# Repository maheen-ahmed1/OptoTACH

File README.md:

# OptoTACH
### A Precision Non-Contact Optical Tachometer Built Entirely Without a Microcontroller

**OptoTACH** is a discrete hardware engineering project that implements a full-featured, 4-digit optical tachometer (0–9999 RPM / RPS / Event Counter) using **pure CMOS logic and analog timing circuits**—completely free of microcontrollers, firmware, and software dependencies.

## ⚡ Showcase & Physical Verification

| 3D CAD Visualization | Assembled Hardware Prototype | Live Calibration vs Commercial Bench Standard |
| :---: | :---: | :---: |
|  |  |  |
| *Raytraced 3D model in KiCad* | *Physical board with socketed DIP ICs* | *Benchmark vs Lutron DT-2236 (2267 vs 2280 RPM)* |

### 🎬 Live Bench Demo
The board measures the rotational velocity of a high-speed cooling fan equipped with a reflective marker. The reading automatically updates every 4 seconds with zero display jitter.

<p align="center">
  
  <br>
  <em>Live demonstration: OptoTACH benchmarked alongside an industrial Lutron DT-2236 photo/contact tachometer.</em>
  <br>
  <a href="media/optotach_demo.mp4">▶️ Download / View Full 1080p Demo Video (2 min 50 sec, 35 MB MP4)</a>
</p>

## 🔄 Inspiration & Circuit Redesign (Overcoming IC Obsolescence)

This project was inspired by the original design published by [Mousa Simple Projects (August 2020)](https://www.mousa-simple-project.com/2020/08/non-contact-tachometer-without.html). However, **the schematic in OptoTACH is fundamentally redesigned** due to component obsolescence and supply-chain constraints.

### The Problem: Obsolescence of the CD40110
The original 2020 design relied on 4 × **CD40110** integrated circuits. The CD40110 incorporates an up/down decade counter, 7-segment decoder, and an internal display latch into a single package. Because the CD40110 has been largely discontinued and is unobtainable in South Asian markets (including Bangladesh), building the circuit directly from the original schematic was impossible.

### The Solution: Re-engineering with the CD4026BE
OptoTACH replaces the obsolete chips with the widely available **CD4026BE** (decade counter with 7-segment decoder). However, **the CD4026 has no internal display latch**. Without a latch, displaying raw pulses as they accumulate during a 1-second counting window would result in an illegible rolling blur.

To solve this without adding extra counter or latch ICs, OptoTACH introduces a synchronized **digital gating & display blanking mechanism**:

| Feature / Subsystem | Original Mousa Circuit (2020) | OptoTACH v1.0 (Redesigned) | Why the Change Matters |
| :--- | :--- | :--- | :--- |
| **Counter ICs** | 4 × **CD40110** (Obsolete / Discontinued) | 4 × **CD4026BE** (Standard / Readily Available) | Overcomes supply-chain unavailability |
| **Display Storage** | Internal CD40110 Display Latch | **Digital Blanking Window (CD4026 Pin 3 `DE`)** | Enables rock-solid readout without latch ICs |
| **Gating Timing** | Continuous asynchronous display | **1.000 s Gate once every 4.000 s** | Digits blank during 1 s count; hold static for 3 s |
| **Gate Derivation** | R/C & basic logic | **Exact Quartz Binary Division** ($Q_4 \text{ AND } Q_5$) | Zero drift (<0.005%) derived from 32.768 kHz crystal |
| **Silicon Overhead** | Spare gates left unused | **100% Gate Utilization of CD4093** | Blanking & gating use spare Schmitt NAND gates (0 added ICs) |
| **Operating Modes** | Single fixed mode | **3 Switchable Modes** (RPM, RPS, Counter) | Onboard 4-position DIP switch (`SW1`) |
| **Physical PCB** | Prototype breadboard / perfboard | **Production 2-Layer 100×100mm PCB** | Socketed ICs, ground planes, DFM compliant |

## 🎯 Key Specifications

| Parameter | Specification | Notes / Hardware Source |
| :--- | :--- | :--- |
| **Measurement Range** | **0 – 9,999 RPM** (or RPS / Events) | 4-digit common-cathode 7-segment display (`DS1`–`DS4`) |
| **Measurement Modes** | **RPM**, **RPS**, and **Continuous Counter** | Configured via onboard 4-way DIP switch (`SW1`) |
| **Sensor Type** | Vishay **TCRT5000** Optical Reflex Sensor | 950 nm IR emitter + phototransistor; 0.2–15 mm sensing gap |
| **Timebase Reference** | **32.768 kHz Quartz Crystal** (`Y1`) | Division via dual `CD4060BE` ripple counters; drift < 0.005% |
| **Measurement Window** | **1.000 s Gate every 4.000 s** | Digital AND gating (`Q4` & `Q5`) via Schmitt NAND (`CD4093`) |
| **Multiplier Ratio** | **×60 Pulse Multiplier** (for direct RPM readout) | Dual `CD4017` cascade gating a high-frequency `NE555` burst |
| **Operating Supply** | **5.0 V – 6.0 V DC** (4 × AA cells or bench PSU) | Reverse-polarity protected with onboard bulk decoupling |
| **PCB Dimensions** | **100.0 × 100.0 mm**, 2 layers, FR-4 | 100% Through-Hole Technology (THT) for easy hand assembly |
| **Fabrication State** | **JLCPCB Ready** (DRC 0/0, ERC 0/0) | Gerbers, BOM, drill files, and assembly maps verified |

## 🧠 System Architecture & Circuit Operation

```
                                    +-----------------------------------------------+
                                    |               MODE SELECT (SW1)               |
                                    |   RPM: 0110   |   RPS: 0101   |   CNT: 1000   |
                                    +-----------------------+-----------------------+
                                                            |
 [Target Shaft]                                             v
  +----------+       +---------------+       +------------------------------+       +-------------------+
  |Reflective| ----> |   TCRT5000    | ----> | Optical Conditioning & Burst | ----> |   4-Digit CD4026  |
  |  Marker  |       | Sensor (U1)   |       | Multiplier (NE555 + CD4017)  |       |   Counter Chain   |
  +----------+       +---------------+       +------------------------------+       | (U11,U12,U13,U14) |
                                                            ^                       +---------+---------+
                                                            |                                 |
 [Quartz Timebase]                                          | Gate Signal                     v
  +----------+       +---------------+       +--------------+---------------+       +-------------------+
  |32.768 kHz| ----> | 2 x CD4060BE  | ----> |   CD4093 NAND Logic Gate     | ----> | 4 x 7-Segment LED |
  | Crystal  |       | Dividers      |       |  (1.0s Gate / 4.0s Period)   |       |  Displays (DS1-4) |
  +----------+       +---------------+       +------------------------------+       +-------------------+
                                                            | Display Blanking
                                                            +---------------------------------> Pin 3 (DE)
```

### 1. Digital Quartz Timebase
The 1.000-second count window is derived with zero passive R/C timing dependencies:
$$\text{Gate Period} = \frac{32,768\text{ Hz}}{2^{12} \times 2^{5}} = 0.25\text{ Hz} \quad (4.000\text{ seconds})$$
A logical AND combination of the `CD4060` outputs $Q_4$ (0.5 Hz, 50% duty) and $Q_5$ (0.25 Hz, 50% duty) generates an active gate window of exactly $1.000\text{ s}$ once every $4\text{ s}$.

### 2. ×60 Pulse Burst Multiplier (RPM Conversion)
At 1 pulse per revolution, counting for 1 second yields Revolutions Per Second (RPS). To display Revolutions Per Minute (RPM) directly without software:
1. Each detected optical edge triggers a high-speed `NE555` oscillator burst.
2. Two cascaded `CD4017` decade counters count exactly **60 pulses** and shut off the oscillator.
3. The resulting 60 pulses feed into the `CD4026` display counter chain for every revolution, achieving an exact direct RPM conversion.

### 3. Mode Selection Truth Table
An onboard 4-pole DIP switch (`SW1`) configures the instrument mode:

| Mode | Switch 1 | Switch 2 | Switch 3 | Switch 4 | Functional Behavior |
| :--- | :---: | :---: | :---: | :---: | :--- |
| **RPM** | OFF | **ON** | **ON** | OFF | 1 s gate, ×60 burst multiplier enabled (Direct RPM readout) |
| **RPS** | OFF | **ON** | OFF | **ON** | 1 s gate, direct sensor pulse routing (Direct RPS readout) |
| **CNT** | **ON** | OFF | OFF | OFF | Continuous event counter; display permanently enabled |

### 4. Integrated Circuit Roles & Signal Flow

| RefDes | Part Number | Package | Primary Circuit Role / Subsystem |
| :--- | :--- | :--- | :--- |
| **`U1`** | **TCRT5000** | 4-pin Optical | Reflective optical sensor (950 nm IR LED + phototransistor) |
| **`U2`** | **CD4093BE** | DIP-14 | Quad 2-input Schmitt NAND (gating window logic & display blanking) |
| **`U3`** | **PC817** | DIP-4 | Optical trigger galvanic isolation & pulse conditioning |
| **`U4`** | **NE555P** | DIP-8 | Burst gate monostable latch (active burst control) |
| **`U5`** | **PC817** | DIP-4 | Gate reset isolation & pulse transmission |
| **`U6`** | **NE555P** | DIP-8 | Astable burst clock oscillator ($f \approx 4.8\text{ kHz}$) |
| **`U7`** | **CD4017BE** | DIP-16 | 5-stage Johnson decade counter (burst units: $\div 10$) |
| **`U8`** | **CD4017BE** | DIP-16 | 5-stage Johnson decade counter (burst tens: $\div 6$, auto-reset at 60) |
| **`U9`** | **CD4060BE** | DIP-16 | 14-stage ripple counter & 32.768 kHz oscillator ($\div 2^{12} = 8\text{ Hz}$) |
| **`U10`** | **CD4060BE** | DIP-16 | 14-stage ripple counter ($\div 2^4 = 0.5\text{ Hz}, \div 2^5 = 0.25\text{ Hz}$) |
| **`U11`** | **CD4026BE** | DIP-16 | Decade counter & 7-segment decoder (Digit 1 - LSD) |
| **`U12`** | **CD4026BE** | DIP-16 | Decade counter & 7-segment decoder (Digit 2 - Tens) |
| **`U13`** | **CD4026BE** | DIP-16 | Decade counter & 7-segment decoder (Digit 3 - Hundreds) |
| **`U14`** | **CD4026BE** | DIP-16 | Decade counter & 7-segment decoder (Digit 4 - MSD) |
| **`DS1–4`**| **7SEG-CC** | 10-pin DIP | 0.56" Common-Cathode red LED displays |

## 🔬 Bench Validation & Accuracy Analysis

The assembled hardware was benchmarked in an instrumentation laboratory using a calibrated **Lutron DT-2236 Photo/Contact Tachometer** on a variable-speed brushless DC blower:

| Reference Instrument (Lutron DT-2236) | OptoTACH v1.0 Measured Value | Absolute Deviation | Error (%) | Validation Result |
| :---: | :---: | :---: | :---: | :---: |
| **1,007 RPM** | **1,020 RPM** | +13 RPM | +1.29% | Within $\pm 1$ count ($\pm 60$ RPM) |
| **2,267 RPM** | **2,280 RPM** | +13 RPM | +0.57% | Within $\pm 1$ count ($\pm 60$ RPM) |
| **2,434 RPM** | **2,438 RPM** | +4 RPM | **+0.16%** | High-precision alignment |

> **Quantisation Theory:** In RPM mode with a 1-pulse target marker and a 1-second gate, the fundamental digital resolution is **60 RPM per count**. Any reading within $\pm 60$ RPM of the continuous reference is within theoretical limits. Increasing target markers (e.g., 2 or 4 reflective strips) scales resolution down proportionally.

## 📐 Schematic & Circuit Diagram

The complete schematic was designed in KiCad (clean ERC: 0 errors, 0 warnings).

<p align="center">
  
  <br>
  <em>OptoTACH v1.0 Full Schematic Sheet. Vector PDF available in <a href="fabrication/tach_v1.0_schematic.pdf">fabrication/tach_v1.0_schematic.pdf</a>.</em>
</p>

## 🛠️ PCB Layout & Hardware Design

The printed circuit board was designed from scratch in KiCad with rigorous DFM standards:

- **Dimensions:** 100 mm × 100 mm (optimised for JLCPCB 5-for-\$2 standard manufacturing tier)
- **Layer Stack:** 2 layers, 1.6 mm FR-4, 1 oz copper
- **Ground Strategy:** Solid continuous ground pours on both top and bottom layers, interconnected via stitched return vias
- **Corner Fillets:** Smooth $R = 5\text{ mm}$ rounded corners on `Edge.Cuts` for enclosure fit and ergonomic handling
- **Mounting:** 4 × M3 (3.2 mm NPTH) mounting holes routed with clear copper/keepout zones
- **Serviceability:** All 13 integrated circuits are socketed in dual-in-line (DIP) packages, allowing easy replacement or debugging
- **Silkscreen Guide:** Onboard mode selection table and resistor group markings embedded directly on `F.SilkS`

| Isometric Perspective | Top Layer Orthogonal | Bottom Layer / Solder Side |
| :---: | :---: | :---: |
|  |  |  |

> **Interactive 3D Viewer:** You can inspect and rotate the complete 3D assembly in your browser via GitHub's native 3D viewer by clicking [`media/optotach_3d_model.glb`](media/optotach_3d_model.glb).

## 📂 Repository Structure

```text
OptoTACH/
├── README.md                          # Repository portfolio overview & documentation
├── LICENSE                            # MIT Open Source Hardware License
├── .gitignore                         # KiCad EDA & OS build artifact filter
│
├── hardware/                          # KiCad Source Project (EDA Files)
│   ├── tach_v1.0.kicad_pro            # KiCad project definition
│   ├── tach_v1.0.kicad_sch            # Full schematic sheet (ERC: 0 errors)
│   ├── tach_v1.0.kicad_pcb            # PCB layout (DRC: 0 errors / 0 unconnected)
│   ├── tach_v1.0.kicad_dru            # DRC custom design rules
│   ├── tach_v1.0.kicad_prl            # Project local settings
│   ├── sym-lib-table & fp-lib-table   # Local symbol & footprint library tables
│   ├── tach_lib.kicad_sym             # Custom schematic symbol library
│   └── tach_fp.pretty/                # Custom footprint library (displays, ICs)
│
├── fabrication/                       # Ready-to-Order Manufacturing Package
│   ├── tach_v1.0_gerbers_jlcpcb.zip   # 1-Click Gerber & Drill archive for JLCPCB / PCBWay
│   ├── gerbers/                       # Unpacked RS-274X Gerber & Excellon drill files
│   ├── BOM_OptoTACH_v1.0.csv          # Complete structured Bill of Materials
│   ├── tach_v1.0_assembly.pdf         # Assembly and component reference drawing
│   ├── tach_v1.0_fitted_parts.pdf     # Visual parts fitting and orientation map
│   ├── tach_v1.0_fitted_parts.png     # High-resolution visual parts placement guide
│   ├── tach_v1.0_schematic.pdf        # High-resolution printable schematic sheet
│   └── SHOPPING_LIST.md               # Sourcing notes, LCSC part numbers & socket guide
│
├── simulation/                        # Behavioral Model & Timing Sweep Suite
│   ├── sweep.py                       # Behavioral Python simulation of counting dynamics
│   ├── mksvg.py                       # Vector SVG accuracy curve generator
│   ├── mkchart.py                     # Interactive HTML report generator
│   ├── sweep_report.html              # Standalone interactive browser accuracy report
│   ├── sweep.json                     # Raw sweep data points (0.5 Hz resolution)
│   ├── tach.net                       # Extracted netlist for timing trace
│   └── figures/                       # Rendered frequency & error curves
│
├── docs/                              # Technical Documentation
│   ├── OptoTACH_v1.0_Technical_Report.pdf # 38-page complete technical & verification report
│   ├── BRING_UP_GUIDE.md              # Staged bench test & troubleshooting procedure
│   └── TACHOMETER_ACCURACY_REPORT.md  # Timing simulation & quantisation study
│
└── media/                             # Visual & Interactive Demonstration Assets
    ├── optotach_demo.gif              # High-framerate looping README demonstration
    ├── optotach_demo.mp4              # Full 1080p bench demo video (35 MB H.264)
    ├── optotach_schematic.png         # High-resolution wiring schematic image
    ├── optotach_live_validation.jpg   # Benchmark capture vs Lutron DT-2236
    ├── optotach_prototype.jpeg        # Assembled hardware photograph
    ├── optotach_display_powered.jpeg  # Active 7-segment display photograph
    ├── optotach_3d_render.png         # KiCad 3D raytraced top view
    ├── optotach_3d_angle.png          # KiCad 3D angled view
    ├── optotach_3d_top.png            # KiCad 3D top view
    ├── optotach_3d_back.png           # KiCad 3D rear view
    ├── optotach_3d_model.glb          # Interactive 3D GLTF mesh model
    └── README_VIDEO_NOTE.md           # Video encoding & GitHub hosting notes
```

## 🚀 How to Recreate This Project

### 1. Order the PCB
1. Download [`fabrication/tach_v1.0_gerbers_jlcpcb.zip`](fabrication/tach_v1.0_gerbers_jlcpcb.zip).
2. Upload the ZIP file directly to [JLCPCB](https://jlcpcb.com/) or [PCBWay](https://www.pcbway.com/).
3. Default settings work out-of-the-box:
   - **Dimensions:** 100 × 100 mm
   - **Layers:** 2
   - **PCB Thickness:** 1.6 mm
   - **Solder Mask:** Black (or your choice of color)
   - **Silkscreen:** White

### 2. Source the Components
Review the detailed [Component Shopping List](fabrication/SHOPPING_LIST.md) and [BOM CSV](fabrication/BOM_OptoTACH_v1.0.csv). Key ICs and precision timing parts:

| Component | Quantity | Designation | Key Sourcing Notes |
| :--- | :---: | :--- | :--- |
| **CD4026BE** | 4 | `U11`, `U12`, `U13`, `U14` | Decade Counter / 7-Segment Decoder (DIP-16) |
| **CD4060BE** | 2 | `U9`, `U10` | 14-Stage Ripple Binary Counter / Oscillator (DIP-16) |
| **CD4017BE** | 2 | `U7`, `U8` | 5-Stage Johnson Decade Counter (DIP-16) |
| **CD4093BE** | 1 | `U2` | Quad 2-Input NAND Schmitt Trigger (DIP-14) |
| **NE555P** | 2 | `U4`, `U6` | Precision Bipolar Timer (DIP-8) |
| **PC817** | 2 | `U3`, `U5` | High-Isolation Optocoupler (DIP-4) |
| **TCRT5000** | 1 | `U1` | Reflective Optical Sensor with Phototransistor Output |
| **32.768 kHz** | 1 | `Y1` | Cylindrical Quartz Tuning Fork Crystal ($3 \times 8\text{ mm}$) |
| **7-Segment Display**| 4 | `DS1`, `DS2`, `DS3`, `DS4` | Common-Cathode 0.56" Red Displays |
| **DIP Switch** | 1 | `SW1` | 4-position 2.54 mm pitch DIP switch |

### 3. Assembly Checklist
Follow the visual layout in [`fabrication/tach_v1.0_fitted_parts.pdf`](fabrication/tach_v1.0_fitted_parts.pdf):
1. Solder all passive resistors (using the onboard $220\ \Omega$ segment resistor group).
2. Install small ceramic capacitors ($22\text{ pF}$, $100\text{ nF}$) and diodes (`1N4148`).
3. Solder IC sockets before inserting integrated circuits (prevents thermal damage).
4. Solder DIP switch `SW1`, power terminal block, and reset button.
5. Solder the four 7-segment displays (`DS1`–`DS4`) and the `TCRT5000` sensor.
6. Insert ICs into sockets and power with 5.0 V–6.0 V (4 × AA battery holder recommended). Follow the staged test procedure in [`docs/BRING_UP_GUIDE.md`](docs/BRING_UP_GUIDE.md) to safely bring up each subsystem.

## 📚 Technical Documentation & Simulation Suite

- 📖 **[OptoTACH Technical Report (38 Pages)](docs/OptoTACH_v1.0_Technical_Report.pdf):** Full engineering documentation covering circuit equations, component tolerances, bring-up procedures, and board revision history.
- 🛠️ **[Hardware Bring-Up & Test Procedure](docs/BRING_UP_GUIDE.md):** 7-stage bench testing procedure with power-rail cold checks, probe test points, and troubleshooting matrix.
- 📊 **[Tachometer Accuracy & Simulation Report](docs/TACHOMETER_ACCURACY_REPORT.md):** Behavioral analysis of counting chain dynamics, frequency ceilings, and quantisation error.
- 📈 **[Interactive Browser Accuracy Report](simulation/sweep_report.html):** Open in any browser to inspect interactive frequency vs error curves.

To run the simulation locally:
```bash
cd simulation
python sweep.py     # Generates raw sweep.json
python mksvg.py     # Generates vector SVG curves
python mkchart.py   # Renders sweep_report.html
```

## 👨‍💻 Project Team & Attribution

Developed at **Ahsanullah University of Science and Technology (AUST)**  
Department of Electrical and Electronic Engineering  
*Course: Instrumentation Laboratory (EEE 3212)*

- **Sarkar Maheen Ahmed**
- **Amir Hamza Talib**
- **Azmain Muksit Anam**
- **Nahinul Islam Prottoy**
- **Lion Ahmmed Fahim**

*Concept originally inspired by [Mousa Simple Projects (2020)](https://www.mousa-simple-project.com/2020/08/non-contact-tachometer-without.html), re-architected for CD4026 CMOS logic, custom digital gating, and discrete layout.*

## 📜 License

This project is licensed under the **[MIT License](LICENSE)** — feel free to use, modify, and build upon this design for academic, hobby, and commercial applications.

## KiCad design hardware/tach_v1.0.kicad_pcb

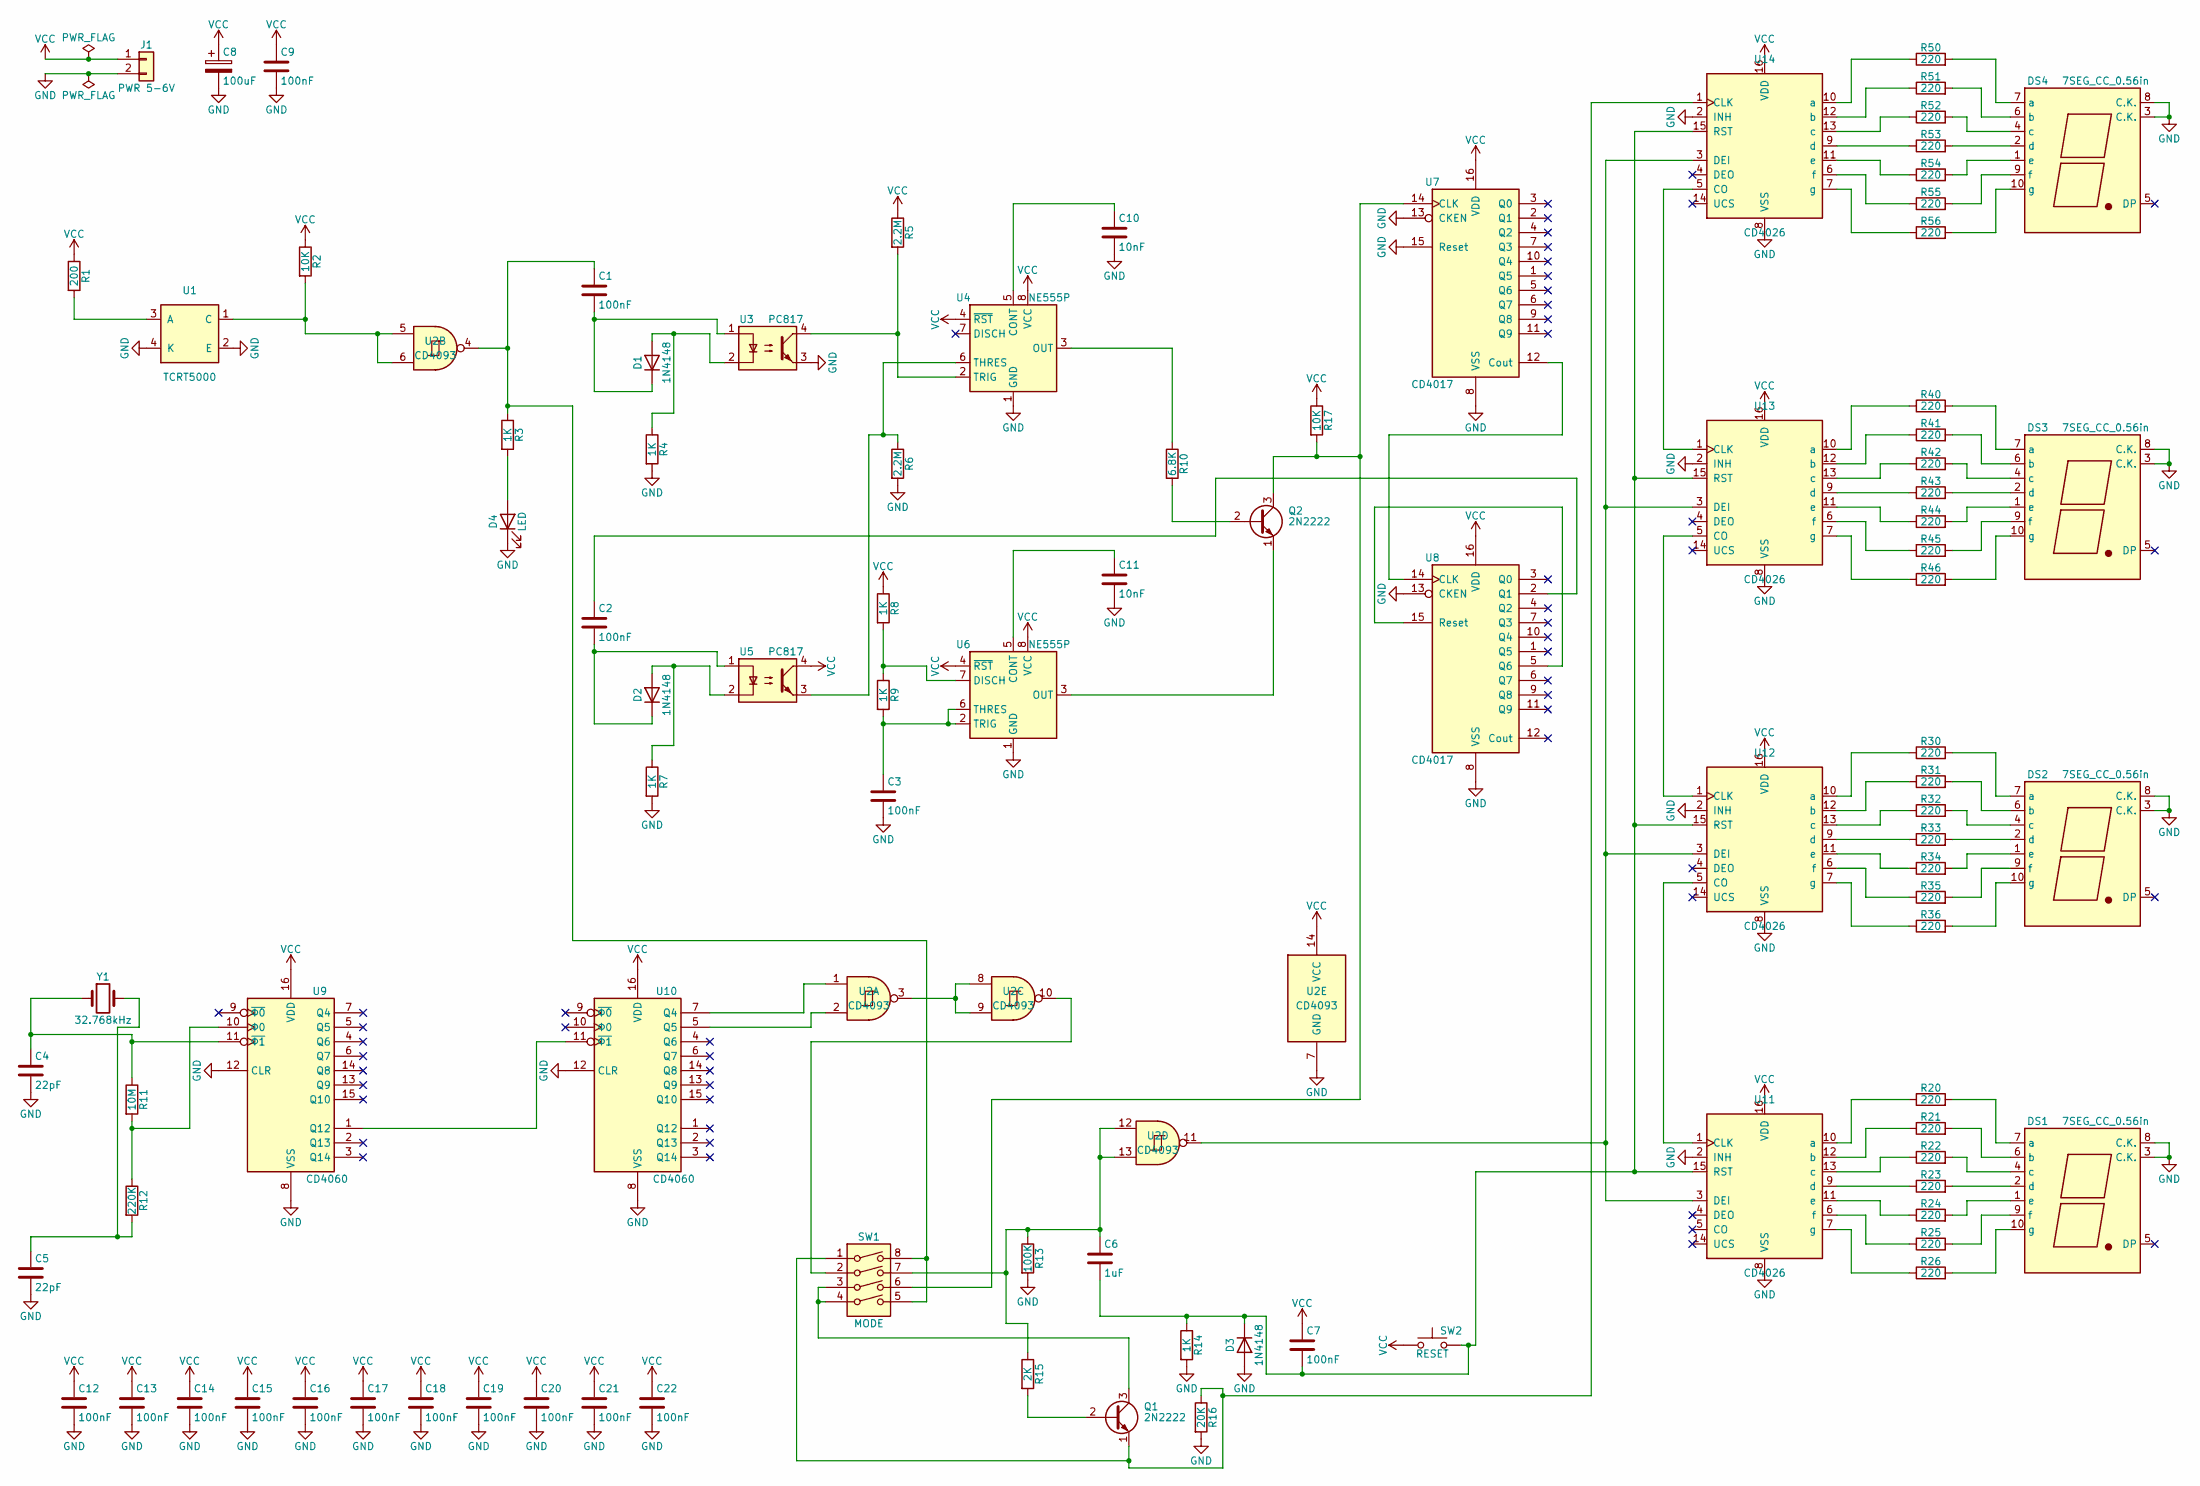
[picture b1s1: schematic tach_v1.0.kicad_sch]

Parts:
C1, C2, C3, C7, C9, C12, C13, C14, C15, C16, C17, C18, C19, C20, C21, C22: 100nF; C_Disc_D3.0mm_W1.6mm_P2.50mm
C4, C5: 22pF; C_Disc_D3.0mm_W1.6mm_P2.50mm
C6: 1uF; C_Disc_D3.0mm_W1.6mm_P2.50mm
C8: 100uF; CP_Radial_D6.3mm_P2.50mm
C10, C11: 10nF; C_Disc_D3.0mm_W1.6mm_P2.50mm
D1, D2, D3: 1N4148; D_DO-35_SOD27_P7.62mm_Horizontal
D4: LED; LED_D5.0mm
DS1, DS2, DS3, DS4: 7SEG_CC_0.56in; 7SegmentLED_LTS6760_LTS6780
J1: PWR 5-6V; PinHeader_1x02_P2.54mm_Vertical
Q1, Q2: 2N2222; TO-92_Inline
R1: 200; R_Axial_DIN0207_L6.3mm_D2.5mm_P7.62mm_Horizontal
R2, R17: 10K; R_Axial_DIN0207_L6.3mm_D2.5mm_P7.62mm_Horizontal
R3, R4, R7, R8, R9, R14: 1K; R_Axial_DIN0207_L6.3mm_D2.5mm_P7.62mm_Horizontal
R5, R6: 2.2M; R_Axial_DIN0207_L6.3mm_D2.5mm_P7.62mm_Horizontal
R10: 6.8K; R_Axial_DIN0207_L6.3mm_D2.5mm_P7.62mm_Horizontal
R11: 10M; R_Axial_DIN0207_L6.3mm_D2.5mm_P7.62mm_Horizontal
R12: 220K; R_Axial_DIN0207_L6.3mm_D2.5mm_P7.62mm_Horizontal
R13: 100K; R_Axial_DIN0207_L6.3mm_D2.5mm_P7.62mm_Horizontal
R15: 2K; R_Axial_DIN0207_L6.3mm_D2.5mm_P7.62mm_Horizontal
R16: 20K; R_Axial_DIN0207_L6.3mm_D2.5mm_P7.62mm_Horizontal
R20, R21, R22, R23, R24, R25, R26, R30, R31, R32, R33, R34, R35, R36, R40, R41, R42, R43, R44, R45, R46, R50, R51, R52, R53, R54, R55, R56: 220; R_Axial_DIN0207_L6.3mm_D2.5mm_P7.62mm_Horizontal
SW1: MODE; SW_DIP_SPSTx04_Slide_9.78x12.34mm_W7.62mm_P2.54mm
SW2: RESET; SW_PUSH_6mm
U1: TCRT5000; TCRT5000_NoClip
U2: CD4093; DIP-14_W7.62mm_LongPads
U3, U5: PC817; DIP-4_W7.62mm_LongPads
U4, U6: NE555P; DIP-8_W7.62mm_LongPads
U7, U8: CD4017; DIP-16_W7.62mm_LongPads
U9, U10: CD4060; DIP-16_W7.62mm_LongPads
U11, U12, U13, U14: CD4026; DIP-16_W7.62mm_LongPads
Y1: 32.768kHz; Crystal_C38-LF_D3.0mm_L8.0mm_Vertical

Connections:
/BURST: Q2.3 (C), R17.2, SW1.6, U7.14 (CLK)
/BURST_DONE: C2.1, U8.2 (Q1)
/CARRY_HUNDREDS: U11.1 (CLK), U12.5 (CO)
/CARRY_TENS: U12.1 (CLK), U13.5 (CO)
/CARRY_UNITS: U13.1 (CLK), U14.5 (CO)
/CLK_8HZ: U9.1 (Q12), U10.11 (~Φ1)
/CNT_CLK: Q1.1 (E), R16.1, SW1.1, U14.1 (CLK)
/CO10: U7.12 (Cout), U8.14 (CLK)
/CV1: C10.1, U4.5 (CONT)
/CV2: C11.1, U6.5 (CONT)
/DISP_EN: U2.11, U11.3 (DEI), U12.3 (DEI), U13.3 (DEI), U14.3 (DEI)
/DIV6_RST: U8.5 (Q6), U8.15 (Reset)
/GATE: SW1.2, U2.10
/GATED_IN: Q1.3 (C), SW1.3, SW1.4
/GATE_N: U2.3, U2.8, U2.9
/GATE_SEL: C6.1, R13.1, R15.1, SW1.7, U2.12, U2.13
/GND: C3.2, C4.2, C5.2, C8.2, C9.2, C10.2, C11.2, C12.2, C13.2, C14.2, C15.2, C16.2, C17.2, C18.2, C19.2, C20.2, C21.2, C22.2, D3.2 (A), D4.1 (K), DS1.3 (C.K.), DS1.8 (C.K.), DS2.3 (C.K.), DS2.8 (C.K.), DS3.3 (C.K.), DS3.8 (C.K.), DS4.3 (C.K.), DS4.8 (C.K.), J1.2, R4.2, R6.2, R7.2, R13.2, R14.2, R16.2, U1.2 (E), U1.4 (K), U2.7 (GND), U3.3, U4.1 (GND), U6.1 (GND), U7.8 (VSS), U7.13 (CKEN), U7.15 (Reset), U8.8 (VSS), U8.13 (CKEN), U9.8 (VSS), U9.12 (CLR), U10.8 (VSS), U10.12 (CLR), U11.2 (INH), U11.8 (VSS), U12.2 (INH), U12.8 (VSS), U13.2 (INH), U13.8 (VSS), U14.2 (INH), U14.8 (VSS)
/IR_LED_A: R1.2, U1.3 (A)
/LATCH_Q: R10.1, U4.3 (OUT)
/LED1_a: DS1.7 (a), R20.2
/LED1_b: DS1.6 (b), R21.2
/LED1_c: DS1.4 (c), R22.2
/LED1_d: DS1.2 (d), R23.2
/LED1_e: DS1.1 (e), R24.2
/LED1_f: DS1.9 (f), R25.2
/LED1_g: DS1.10 (g), R26.2
/LED2_a: DS2.7 (a), R30.2
/LED2_b: DS2.6 (b), R31.2
/LED2_c: DS2.4 (c), R32.2
/LED2_d: DS2.2 (d), R33.2
/LED2_e: DS2.1 (e), R34.2
/LED2_f: DS2.9 (f), R35.2
/LED2_g: DS2.10 (g), R36.2
/LED3_a: DS3.7 (a), R40.2
/LED3_b: DS3.6 (b), R41.2
/LED3_c: DS3.4 (c), R42.2
/LED3_d: DS3.2 (d), R43.2
/LED3_e: DS3.1 (e), R44.2
/LED3_f: DS3.9 (f), R45.2
/LED3_g: DS3.10 (g), R46.2
/LED4_a: DS4.7 (a), R50.2
/LED4_b: DS4.6 (b), R51.2
/LED4_c: DS4.4 (c), R52.2
/LED4_d: DS4.2 (d), R53.2
/LED4_e: DS4.1 (e), R54.2
/LED4_f: DS4.9 (f), R55.2
/LED4_g: DS4.10 (g), R56.2
/LED_IND: D4.2 (A), R3.2
/OSC: Q2.1 (E), U6.3 (OUT)
/OSC_DIS: R8.2, R9.1, U6.7 (DISCH)
/OSC_TH: C3.1, R9.2, U6.2 (TRIG), U6.6 (THRES)
/PULSE: C1.1, R3.1, SW1.5, SW1.8, U2.4
/Q1_B: Q1.2 (B), R15.2
/Q2_B: Q2.2 (B), R10.2
/RESET: C6.2, C7.2, D3.1 (K), R14.1, SW2.2, U11.15 (RST), U12.15 (RST), U13.15 (RST), U14.15 (RST)
/RST_A: C2.2, D2.1 (K), U5.1
/RST_K: D2.2 (A), R7.1, U5.2
/SEG1_a: R20.1, U11.10 (a)
/SEG1_b: R21.1, U11.12 (b)
/SEG1_c: R22.1, U11.13 (c)
/SEG1_d: R23.1, U11.9 (d)
/SEG1_e: R24.1, U11.11 (e)
/SEG1_f: R25.1, U11.6 (f)
/SEG1_g: R26.1, U11.7 (g)
/SEG2_a: R30.1, U12.10 (a)
/SEG2_b: R31.1, U12.12 (b)
/SEG2_c: R32.1, U12.13 (c)
/SEG2_d: R33.1, U12.9 (d)
/SEG2_e: R34.1, U12.11 (e)
/SEG2_f: R35.1, U12.6 (f)
/SEG2_g: R36.1, U12.7 (g)
/SEG3_a: R40.1, U13.10 (a)
/SEG3_b: R41.1, U13.12 (b)
/SEG3_c: R42.1, U13.13 (c)
/SEG3_d: R43.1, U13.9 (d)
/SEG3_e: R44.1, U13.11 (e)
/SEG3_f: R45.1, U13.6 (f)
/SEG3_g: R46.1, U13.7 (g)
/SEG4_a: R50.1, U14.10 (a)
/SEG4_b: R51.1, U14.12 (b)
/SEG4_c: R52.1, U14.13 (c)
/SEG4_d: R53.1, U14.9 (d)
/SEG4_e: R54.1, U14.11 (e)
/SEG4_f: R55.1, U14.6 (f)
/SEG4_g: R56.1, U14.7 (g)
/SENS_RAW: R2.2, U1.1 (C), U2.5, U2.6
/SET_A: C1.2, D1.1 (K), U3.1
/SET_K: D1.2 (A), R4.1, U3.2
/THRES: R6.1, U4.6 (THRES), U5.3
/TRIG: R5.2, U3.4, U4.2 (TRIG)
/T_Q4_0.5HZ: U2.1, U10.7 (Q4)
/T_Q5_0.25HZ: U2.2, U10.5 (Q5)
/VCC: C7.1, C8.1, C9.1, C12.1, C13.1, C14.1, C15.1, C16.1, C17.1, C18.1, C19.1, C20.1, C21.1, C22.1, J1.1, R1.1, R2.1, R5.1, R8.1, R17.1, SW2.1, U2.14 (VCC), U4.4 (~RST), U4.8 (VCC), U5.4, U6.4 (~RST), U6.8 (VCC), U7.16 (VDD), U8.16 (VDD), U9.16 (VDD), U10.16 (VDD), U11.16 (VDD), U12.16 (VDD), U13.16 (VDD), U14.16 (VDD)
/XTAL_DRV: R11.2, R12.1, U9.10 (Φ0)
/XTAL_IN: C4.1, R11.1, U9.11 (~Φ1), Y1.1
/XTAL_OUT: C5.1, R12.2, Y1.2

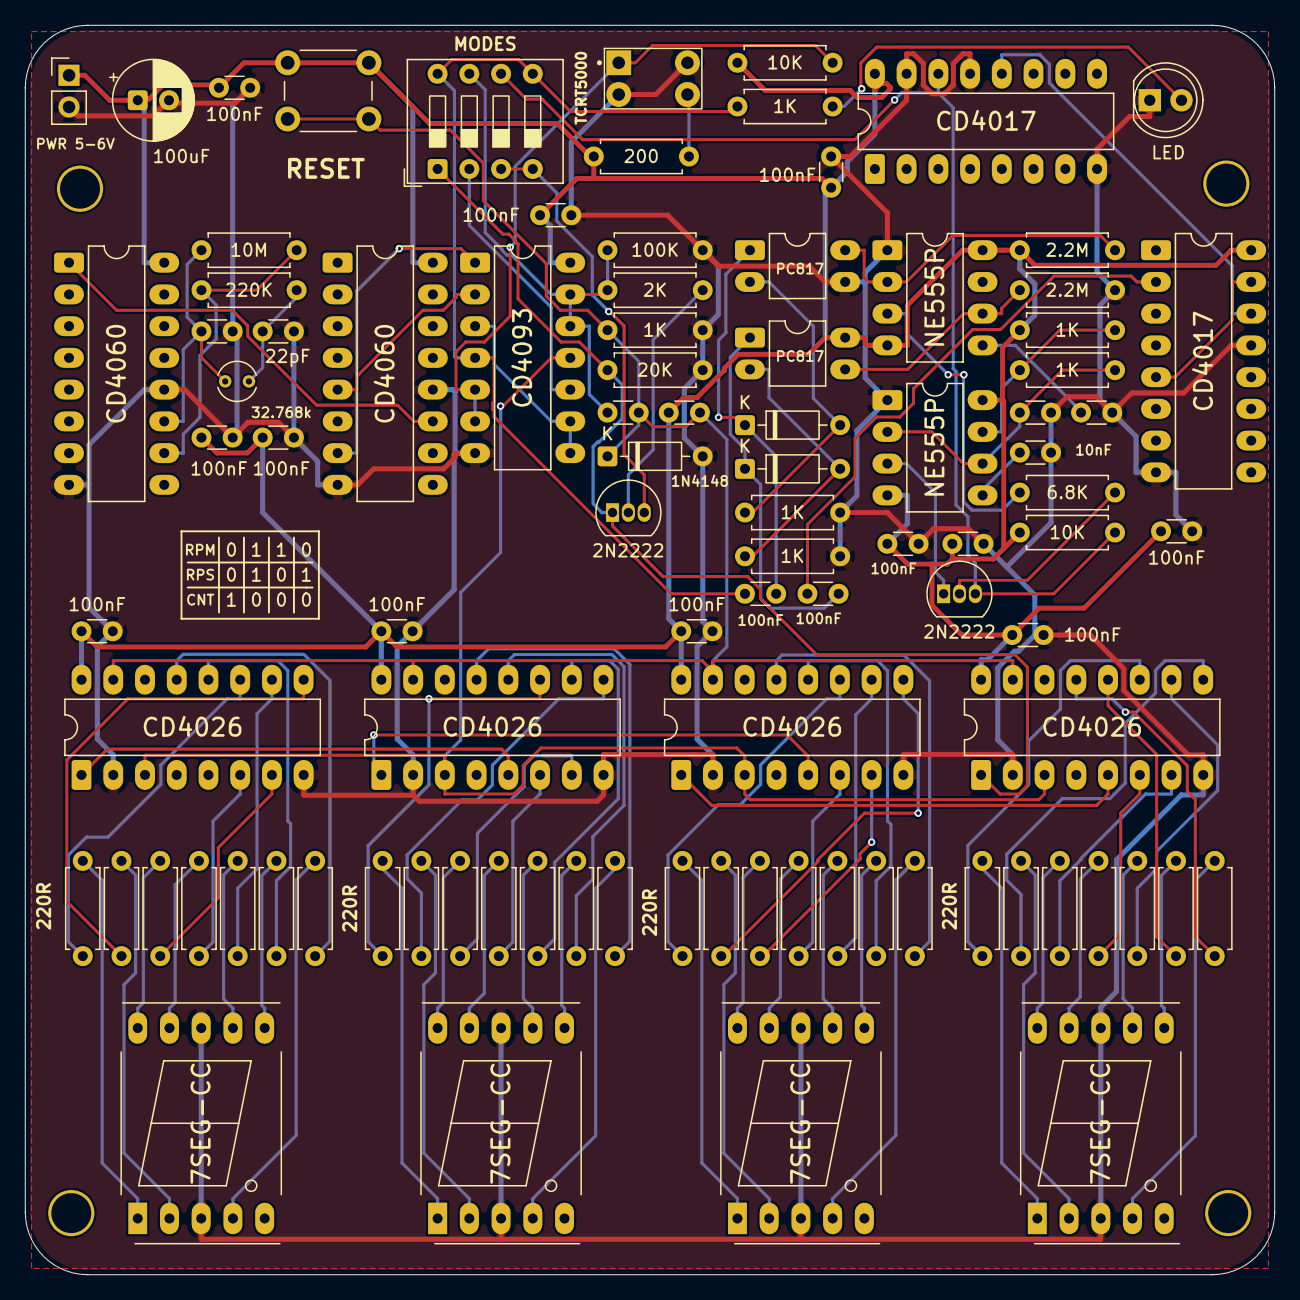
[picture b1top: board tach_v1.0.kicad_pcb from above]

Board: 2 copper layers, 100.0 x 100.0 mm, 99 parts (0 on the bottom side), 96 nets.

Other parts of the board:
H1, H2, H3, H4: MountingHole; MountingHole_3.2mm

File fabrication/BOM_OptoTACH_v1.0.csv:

"Refs","Value","Fit","Footprint","Qty","Source","Store","Notes"
"C1,C2,C7,C9,C12-C22","100nF","100nF","Capacitor_THT:C_Disc_D3.0mm_W1.6mm_P2.50mm","15","Buy","RoboticsBD",""
"C3","100nF","100nF","Capacitor_THT:C_Disc_D3.0mm_W1.6mm_P2.50mm","1","Buy","RoboticsBD","NE555 (U6) burst oscillator - see alternate row below"
"C4,C5","22pF","22pF","Capacitor_THT:C_Disc_D3.0mm_W1.6mm_P2.50mm","2","Buy","RoboticsBD",""
"C6","1uF","1uF","Capacitor_THT:C_Disc_D3.0mm_W1.6mm_P2.50mm","1","Buy","RoboticsBD","Ceramic, NOT electrolytic - this one sees both polarities"
"C8","100uF","100uF","Capacitor_THT:CP_Radial_D6.3mm_P2.50mm","1","In stock","",""
"C10,C11","10nF","10nF","Capacitor_THT:C_Disc_D3.0mm_W1.6mm_P2.50mm","2","Buy","Robotech, Techshop",""
"D1-D3","1N4148","1N4148","Diode_THT:D_DO-35_SOD27_P7.62mm_Horizontal","3","Buy","RoboticsBD",""
"D4","LED","LED","LED_THT:LED_D5.0mm","1","In stock","",""
"DS1-DS4","7SEG_CC_0.56in","7SEG_CC_0.56in","Display_7Segment:7SegmentLED_LTS6760_LTS6780","4","In stock","","COMMON CATHODE. A common-anode part will not light at all."
"J1","PWR 5-6V","PWR 5-6V","Connector_PinHeader_2.54mm:PinHeader_1x02_P2.54mm_Vertical","1","Not fitted","","Not fitted - power leads soldered straight into the J1 holes"
"Q1,Q2","2N2222","2N2222","Package_TO_SOT_THT:TO-92_Inline","2","Buy","RoboticsBD","TO-92 plastic, not the TO-18 metal can"
"R1","200","220","Resistor_THT:R_Axial_DIN0207_L6.3mm_D2.5mm_P7.62mm_Horizontal","1","Buy","Any shop","Drawn as 200, fit 220 - TCRT5000 IR LED current: 21.6 mA instead of 23.8 mA at 6 V"
"R2,R17","10K","10K","Resistor_THT:R_Axial_DIN0207_L6.3mm_D2.5mm_P7.62mm_Horizontal","2","In stock","",""
"R3,R4,R7-R9,R14","1K","1K","Resistor_THT:R_Axial_DIN0207_L6.3mm_D2.5mm_P7.62mm_Horizontal","6","In stock","",""
"R5,R6","2.2M","2.2M","Resistor_THT:R_Axial_DIN0207_L6.3mm_D2.5mm_P7.62mm_Horizontal","2","In stock","","Replaces the original design's 2M (not a stocked value)"
"R10","6.8K","5.6K","Resistor_THT:R_Axial_DIN0207_L6.3mm_D2.5mm_P7.62mm_Horizontal","1","In stock","","Drawn as 6.8K, fit 5.6K from stock - Q2 base resistor, only needs to saturate the transistor"
"R11","10M","10M","Resistor_THT:R_Axial_DIN0207_L6.3mm_D2.5mm_P7.62mm_Horizontal","1","In stock","",""
"R12","220K","220K","Resistor_THT:R_Axial_DIN0207_L6.3mm_D2.5mm_P7.62mm_Horizontal","1","In stock","",""
"R13","100K","100K","Resistor_THT:R_Axial_DIN0207_L6.3mm_D2.5mm_P7.62mm_Horizontal","1","In stock","",""
"R15","2K","2.2K","Resistor_THT:R_Axial_DIN0207_L6.3mm_D2.5mm_P7.62mm_Horizontal","1","In stock","","Drawn as 2K, fit 2.2K from stock - Q1 base resistor, only needs to saturate the transistor"
"R16","20K","22K","Resistor_THT:R_Axial_DIN0207_L6.3mm_D2.5mm_P7.62mm_Horizontal","1","In stock","","Drawn as 20K, fit 22K from stock - Pulldown on the counter clock line, value not critical"
"R20-R26,R30-R36,R40-R46,R50-R56","220","220","Resistor_THT:R_Axial_DIN0207_L6.3mm_D2.5mm_P7.62mm_Horizontal","28","Buy","Any shop","Segment resistors, 4 digits x 7"
"SW1","MODE","MODE","Button_Switch_THT:SW_DIP_SPSTx04_Slide_9.78x12.34mm_W7.62mm_P2.54mm","1","Buy","RoboticsBD",""
"SW2","RESET","RESET","Button_Switch_THT:SW_PUSH_6mm","1","In stock","",""
"U1","TCRT5000","TCRT5000","tach_fp:TCRT5000_NoClip","1","In stock","",""
"U2","CD4093","CD4093","Package_DIP:DIP-14_W7.62mm_LongPads","1","Buy","ElectronicsBD",""
"U3,U5","PC817","PC817","Package_DIP:DIP-4_W7.62mm_LongPads","2","Buy","RoboticsBD",""
"U4,U6","NE555P","NE555P","Package_DIP:DIP-8_W7.62mm_LongPads","2","Buy","RoboticsBD",""
"U7,U8","CD4017","CD4017","Package_DIP:DIP-16_W7.62mm_LongPads","2","Buy","RoboticsBD",""
"U9,U10","CD4060","CD4060","Package_DIP:DIP-16_W7.62mm_LongPads","2","Buy","RoboticsBD",""
"U11-U14","CD4026","CD4026","Package_DIP:DIP-16_W7.62mm_LongPads","4","Buy","RoboticsBD",""
"Y1","32.768kHz","32.768kHz","Crystal:Crystal_C38-LF_D3.0mm_L8.0mm_Vertical","1","Buy","Techshop",""
"C3 (alt)","22nF","22nF","Capacitor_THT:C_Disc_D3.0mm_W1.6mm_P2.50mm","1","Buy","RoboticsBD","Fit INSTEAD of the 100nF to raise the RPM ceiling from ~4800 to ~21800. Buy both and compare."
